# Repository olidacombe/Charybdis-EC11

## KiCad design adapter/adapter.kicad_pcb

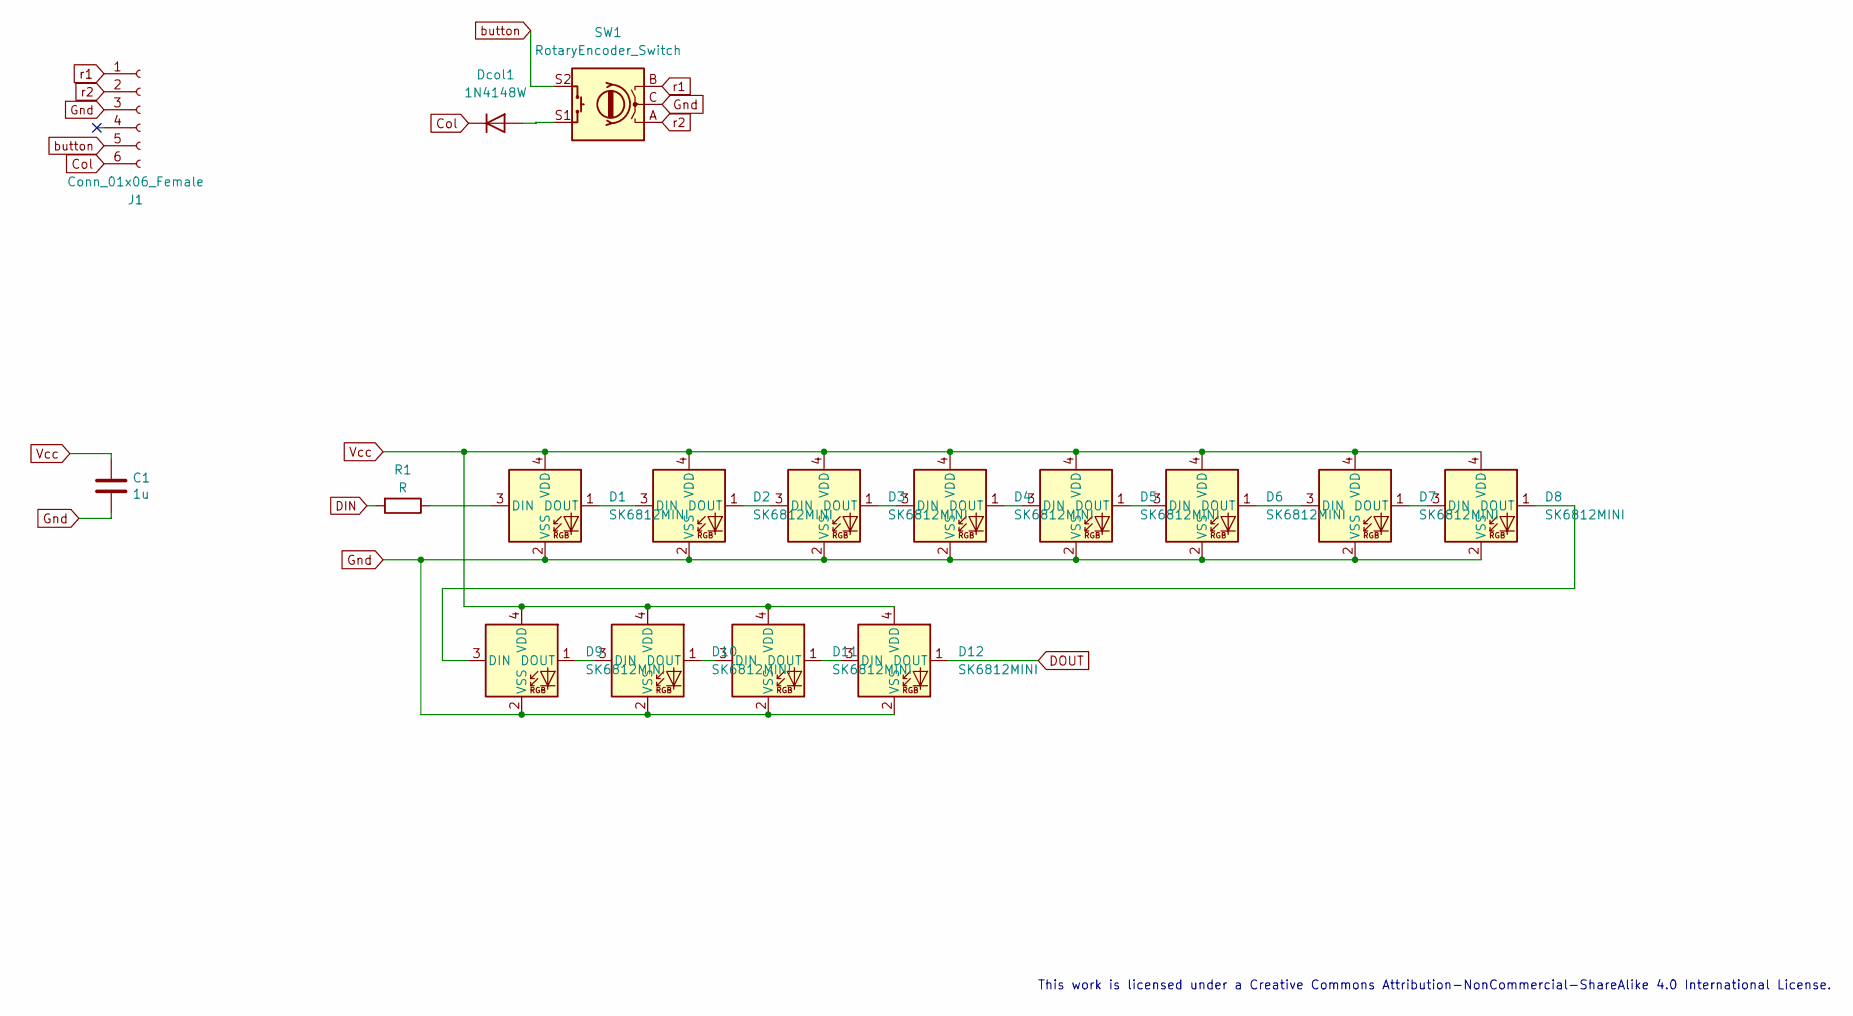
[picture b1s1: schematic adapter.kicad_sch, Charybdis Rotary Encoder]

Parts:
C1: 1u; C_1206_3216Metric_Pad1.33x1.80mm_HandSolder
D1, D2, D3, D4, D5, D6, D7, D8, D9, D10, D11, D12: SK6812MINI; YS-SK6812MINI-E
Dcol1: 1N4148W; D_1206_3216Metric_Pad1.42x1.75mm_HandSolder
J1: Conn_01x06_Female; 6_PinHeader
R1: R; R_1206_3216Metric_Pad1.30x1.75mm_HandSolder
SW1: RotaryEncoder_Switch; RotaryEncoder_Alps_EC11E-Switch_Vertical_H20mm

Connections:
Col: Dcol1.1 (K), J1.6
DIN: R1.2
DOUT: D12.1 (DOUT)
Gnd: C1.2, D1.2 (VSS), D2.2 (VSS), D3.2 (VSS), D4.2 (VSS), D5.2 (VSS), D6.2 (VSS), D7.2 (VSS), D8.2 (VSS), D9.2 (VSS), D10.2 (VSS), D11.2 (VSS), D12.2 (VSS), J1.3, SW1.C
unnamed: D1.3 (DIN), R1.1
unnamed: D1.1 (DOUT), D2.3 (DIN)
unnamed: D2.1 (DOUT), D3.3 (DIN)
unnamed: D3.1 (DOUT), D4.3 (DIN)
unnamed: D4.1 (DOUT), D5.3 (DIN)
unnamed: D5.1 (DOUT), D6.3 (DIN)
unnamed: D6.1 (DOUT), D7.3 (DIN)
unnamed: D7.1 (DOUT), D8.3 (DIN)
unnamed: D8.1 (DOUT), D9.3 (DIN)
unnamed: D9.1 (DOUT), D10.3 (DIN)
unnamed: D10.1 (DOUT), D11.3 (DIN)
unnamed: D11.1 (DOUT), D12.3 (DIN)
unnamed: Dcol1.2 (A), SW1.S1
Vcc: C1.1, D1.4 (VDD), D2.4 (VDD), D3.4 (VDD), D4.4 (VDD), D5.4 (VDD), D6.4 (VDD), D7.4 (VDD), D8.4 (VDD), D9.4 (VDD), D10.4 (VDD), D11.4 (VDD), D12.4 (VDD)
button: J1.5, SW1.S2
r1: J1.1, SW1.B
r2: J1.2, SW1.A

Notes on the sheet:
This work is licensed under a Creative Commons Attribution-NonCommercial-ShareAlike 4.0 International License.

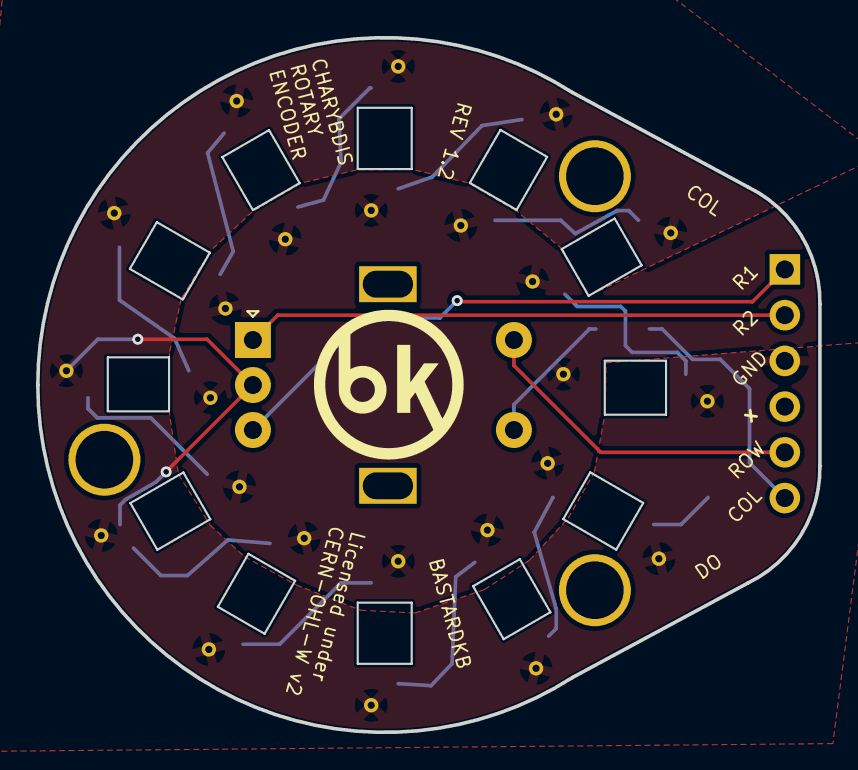
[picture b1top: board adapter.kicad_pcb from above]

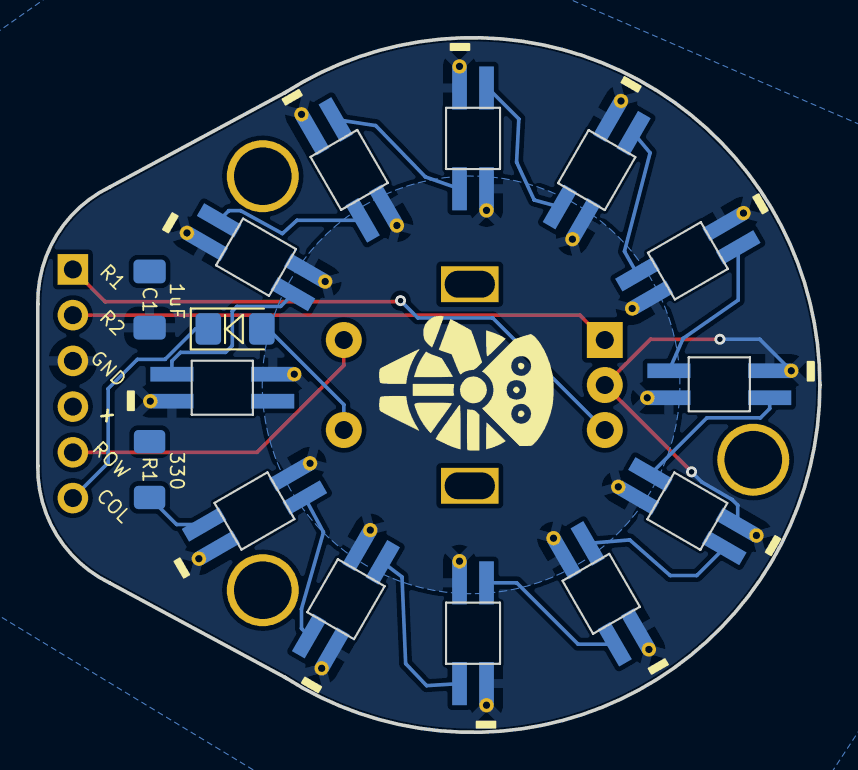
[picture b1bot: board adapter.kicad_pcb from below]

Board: 2 copper layers, 43.5 x 38.6 mm, 17 parts (15 on the bottom side), 19 nets.

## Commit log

2023-09-23 tailor
2023-09-23 rearrange to avoid cable twist
2023-09-23 oh dear - the holes are gone
2023-09-24 route without break
2023-09-24 rendered

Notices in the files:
adapter/adapter.kicad_pcb:
CERN-OHL-W v2
adapter/adapter.kicad_sch:
Licensed under CERN-OHL-W v2
